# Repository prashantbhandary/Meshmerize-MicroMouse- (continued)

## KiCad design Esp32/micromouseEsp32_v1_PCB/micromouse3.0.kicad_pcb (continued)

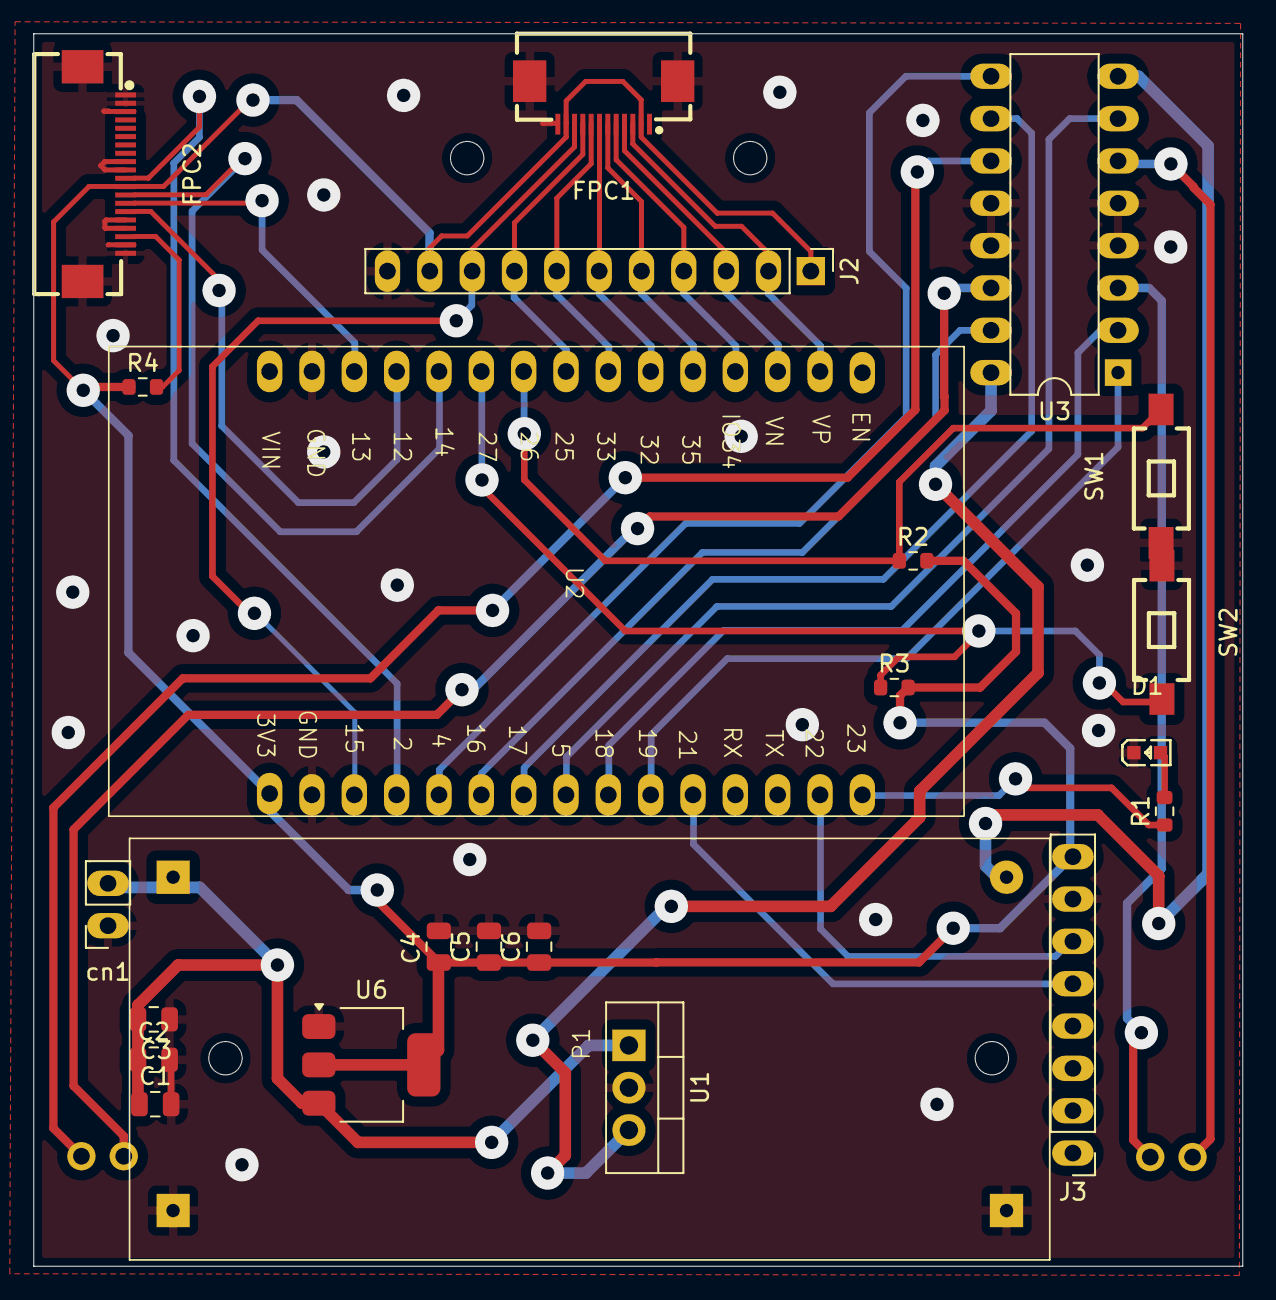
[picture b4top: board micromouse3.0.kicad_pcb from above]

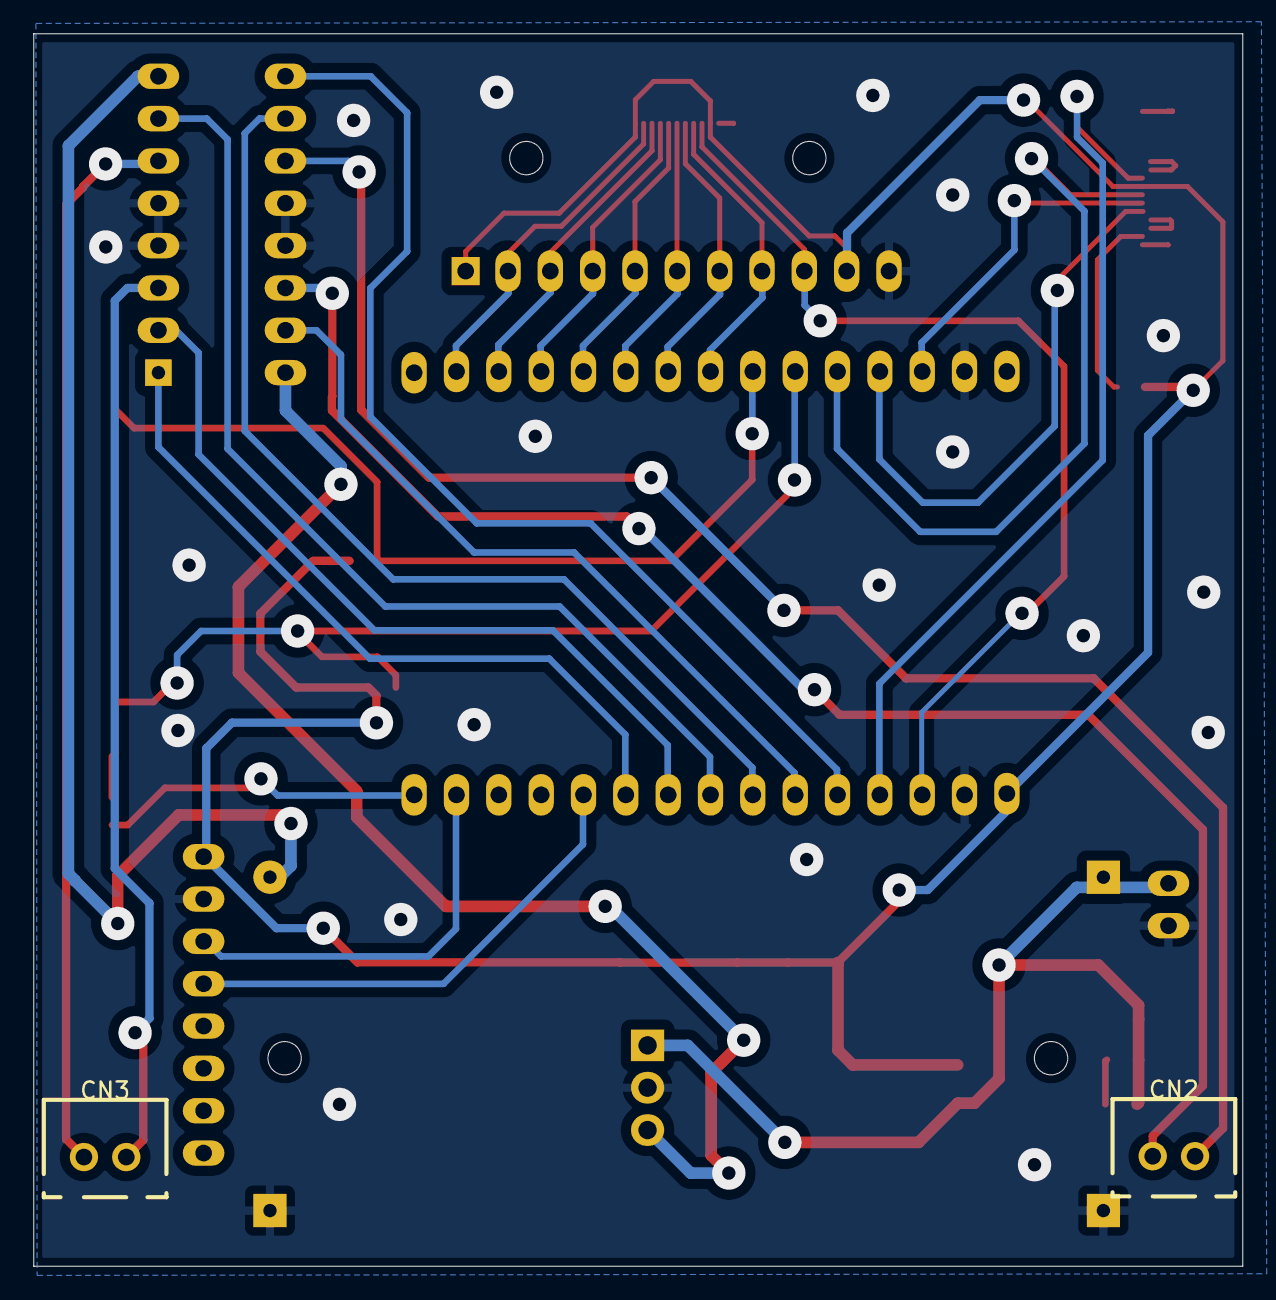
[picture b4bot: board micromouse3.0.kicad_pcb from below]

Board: 2 copper layers, 72.5 x 73.9 mm, 25 parts (2 on the bottom side), 34 nets.

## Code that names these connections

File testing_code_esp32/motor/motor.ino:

#include <SparkFun_TB6612.h>
#define AIN1 18
#define BIN1 17
#define AIN2 5
#define BIN2 16
#define PWMA 19
#define PWMB 4

#define sw1 26
#define sw2 27
#define led 23
int s1;

Motor motor1 = Motor(BIN1, BIN2, PWMB, 1, 1);
Motor motor2 = Motor(AIN1, AIN2, PWMA, 1, 1);

void setup() {
  pinMode(sw1, INPUT);
  pinMode(sw2,INPUT);
  
  pinMode(led, OUTPUT);
  

   s1 = digitalRead(sw1);  //s1 for running bot
  while (s1 == HIGH)
  {
    s1 = digitalRead(sw1);    
  }
  digitalWrite(led,HIGH);

}

void loop() {
  // put your main code here, to run repeatedly:
  forward(motor1, motor2, 200);
  delay(4000);
  // back(motor1, motor2, 200);
  // delay(400);
  // brake(motor1, motor2);
  // delay(50);
  // left(motor1, motor2, 200); 
  // delay(4000);
  // right(motor1, motor2, 200);
  // delay(400);
}

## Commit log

2025-03-26 Upladed all the files of micromouse
2025-03-26 README.md
2025-04-22 Renamed
2025-06-15 added picture
2025-06-15 added
2025-09-25 Updated files of the Micro Mouse with V3, and Esp on pending
